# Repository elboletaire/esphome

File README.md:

ESPHome personal builds and other stuff
=======================================

Don't forget about the `secrets.yaml` file! Secrets used in these scripts:

```yaml
# secrets.yaml
wifi_pass: "your_wifi_password"
wifi_name: "your_wifi_name"
key: "key used to connect to your devices"
```

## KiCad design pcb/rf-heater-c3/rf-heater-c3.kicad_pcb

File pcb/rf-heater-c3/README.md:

# rf-heater-c3

Placa de connexió de 2 capes (FR4 1.6 mm, 43.7 × 30 mm) per a un ESP32-C3 Super Mini amb un mòdul CC1101 868 MHz (format M115, pads castellats). Tota la placa es genera des de `generate.py`.

## Fitxers

- `generate.py`: genera `rf-heater-c3.kicad_pcb` i `.kicad_pro`, rutat amb Freerouting, zones GND, DRC, Gerbers i renders.
- `fab/rf-heater-c3-gerbers.zip`: Gerbers (Cu, Mask, Silk, Paste, Edge.Cuts) i Excellon.
- `render-top.png`, `render-bottom.png`.

## Mapatge de pins

| ESP32-C3 (U1) | GPIO | Net | CC1101 (U2) |
|---|---|---|---|
| 3V3 | - | 3V3 | 1 VCC |
| G | - | GND | 2, 9, 11 GND |
| 4 | GPIO4 | SCK | 4 SCLK |
| 5 | GPIO5 | MISO | 5 SO |
| 6 | GPIO6 | MOSI | 3 SI |
| 7 | GPIO7 | CSN | 8 CSN |
| 10 | GPIO10 | GDO0 | 7 GDO0 |

U2.6 (GDO2) no es connecta. U2.10 (ANT) no té net: és el pad on es solda l'antena de molla.

## Regenerar

```sh
/Applications/KiCad/KiCad.app/Contents/Frameworks/Python.framework/Versions/3.9/bin/python3 -I generate.py
```

Cal Freerouting a `~/.local/share/freerouting/freerouting-2.5.0.jar` i Java (per defecte `brew --prefix openjdk`; es pot fixar amb `JAVA_BIN`). El script sobreescriu els fitxers de sortida.

## BOM

| Ref | Component | Qtat | Notes |
|---|---|---|---|
| U1 | ESP32-C3 Super Mini | 1 | 2 files de 8 forats de 2.54 mm, separades 15.24 mm |
| U2 | Mòdul CC1101 868 MHz (M115) | 1 | 8 pads a la vora de capçalera, 3 a la vora d'antena |
| ANT | Antena de molla 868 MHz | 1 | Soldada al pad 10 |
| C1 | Electrolític 10 µF, radial 5 mm, P 2.00 mm | 1 | Polaritat: el `+` és el pad 1 (3V3) |
| C2 | Ceràmic 100 nF, disc D3 mm, P 2.50 mm | 1 | |
| H1, H2 | Forat M3 (3.2 mm, sense pad) | 2 | Per a cargols M3 |
| - | Pins 2×8 de 2.54 mm | 2 | Opcional, per soldar o endollar el C3 |

## Muntatge

- Soldar primer C2 i C1, després U1 i finalment U2.
- U2: el punt de pin 1 és a la part inferior de la vora de capçalera. Els pads són SMD de 2 × 1 mm que sobresurten de la vora del mòdul: soldar-los amb ferro i una mica de flux.
- Pad 10 (ANT) sense net: només serveix de punt de soldadura per a l'antena. Al voltant hi ha una zona prohibida de 3 mm (sense pistes, vies ni farcit de GND), amb dos corredors per als pads 9 i 11.
- Les posicions dels pads d'antena (`ANT_PAD_OFFSETS`, mesurades des de la cantonada del pin 1) són les del mòdul real que s'ha mesurat. Les mides del mòdul (`MOD_H = 17.4`) i els pads 9 i 11 (1.2 mm) també venen d'aquesta mesura.
- **El `.kicad_pcb` té edicions manuals** (serigrafia, p. ex. el text «elboletaire» i la data, i algunes posicions). Regenerar amb `generate.py` les sobreescriuria: aleshores cal tornar-les a aplicar a mà.

## Notes

- La vora dreta de la placa és a x = 43.7, no a 42.4: així els pads d'antena (que sobresurten 1 mm del mòdul) queden dins la placa amb 0.3 mm de marge.
- El GND no es rutat: el connecten el farcit de les dues capes, tres petites pistes de 0.5 mm (pads 9 i 11 i pad 2 del mòdul cap al farcit), una pista de 0.6 mm des del GND del C3 (U1.2) per la vora superior, i 3 vies d'unió entre capes.
- DRC: 0 errors, 0 unconnected. Avisos: 2 de biblioteca de footprint `rf-heater-c3` (custom, no és a la taula de biblioteques de l'usuari) i 3 de serigrafia tocant la vora (el contorn del C3 és a y = 0).
- Freerouting ha estrenyit alguns segments: 3V3 a 0.375 mm (a prop del C3, a la vora superior), MOSI i SCK a 0.225 mm (prop dels pads). Compleixen el mínim de 0.2 mm, però no els objectius de 0.5 mm (3V3) i 0.3 mm (senyals).

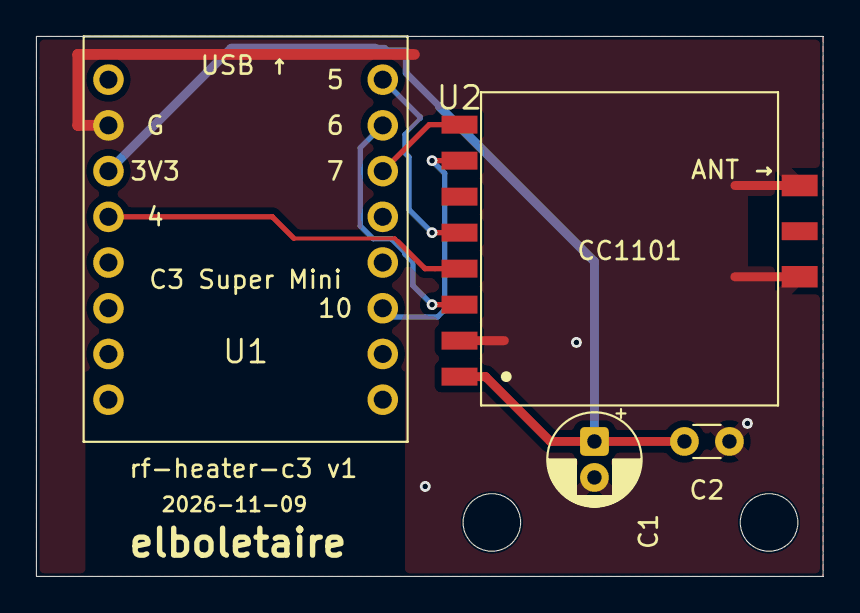
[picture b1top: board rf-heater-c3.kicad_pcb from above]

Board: 2 copper layers, 43.7 x 30.0 mm, 6 parts (0 on the bottom side), 7 nets.

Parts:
C1: 10uF; CP_Radial_D5.0mm_P2.00mm
C2: 100nF; C_Disc_D3.0mm_W1.6mm_P2.50mm
H1, H2: M3; MountingHole_3.2mm_M3
U1: ESP32-C3 Super Mini; ESP32-C3-SuperMini
U2: CC1101 868MHz; CC1101_M115

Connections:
3V3: C1.1, C2.1, U1.3, U2.1
CSN: U1.11, U2.8
GDO0: U1.14, U2.7
GND: C1.2, C2.2, U1.2, U2.2, U2.9, U2.11
MISO: U1.9, U2.5
MOSI: U1.10, U2.3
SCK: U1.4, U2.4

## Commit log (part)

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2025-06-22 Migrate ESPHome CC1101 component to external components architecture
    - Convert custom cc1101.h header to proper ESPHome external component
    - Create components/cc1101/ directory with proper structure:
    - __init__.py: Component configuration and code generation
    - cc1101.h: Header file with CC1101Component and CC1101Sensor classes
    - cc1101.cpp: Implementation with setup, transmission control, and RSSI
    - sensor.py: Sensor platform integration for RSSI monitoring
2025-06-22 Successfully migrate CC1101 component to external components architecture
    - Fix compilation errors and update codeowner to @elboletaire
    - Remove sensor component to simplify implementation (was internal anyway)
    - Fix SPI pin access by using hardcoded pins matching YAML configuration
    - Fix LOG_PIN macro usage by using ESP_LOGCONFIG instead
    - Remove unnecessary sensor includes and implementations
    - Successfully compiles with ESPHome 2025.6.0
2025-06-22 Update RF codes with fresh captures to fix heater OFF command
    - Replace all RF transmission codes with fresh captures from logs.ai
    - Heater ON: Updated with 3 new sequences from power-on logs
    - Heater OFF: Updated with 3 new sequences from power-off logs
    - Maintains same structure: 3 sequences with 120ms delays
    - Should resolve issue where OFF command wasn't working
    - All codes captured from working remote control for accuracy
2025-06-22 fix(cc1101): 🐛 reinit remote_transmitter to fix consecutive signal transmission issue
2025-06-22 chore: cleanup
2025-06-22 chore: add readme
2025-06-22 feat(rf): add switch with shared state with buttons and other utilities
2025-08-07 feat: add probe-thermostat device
2025-11-15 chore(probe thermostat): add battery
2025-12-09 WIP not successful
